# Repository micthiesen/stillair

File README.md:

# stillair

Custom 44-inch direct-drive ceiling fan for quiet overnight air mixing: CubeMars GL100 KV10
gimbal motor, TI MCF8316D sensorless FOC on a custom controller board, ESP32-C6 supervisor
with local-only Apple Home control via Matter (rs-matter), and an independent analog
overspeed backstop.

This repo is the canonical source for everything except the OnShape 3D model:

- [`docs/`](docs/overview.md) — the full design dossier (start at the overview; current work
  state in [docs/STATE.md](docs/STATE.md))
- [`bom/`](bom/README.md) — parts list with purchase tracking
- [`testing/`](testing/README.md) — commissioning matrix with sign-off fields
- [`firmware/`](firmware/) — Rust `no_std` ESP32-C6 supervisor (stub; contract in
  [docs/controls.md](docs/controls.md))
- [`pcb/`](pcb/README.md): authoritative tscircuit source for new boards plus downstream KiCad
  routing and production outputs (requirements in [docs/electrical.md](docs/electrical.md))
- [`cad/`](cad/README.md) — fabrication outputs (specs in [docs/parts.md](docs/parts.md))

Firmware: `cd firmware && cargo build` (stable Rust). Flash the C6 with `cargo run --release` in
`firmware/app` (USB, via `firmware/scripts/flash-app.sh`) or update over the LAN with `esp-ota push`.

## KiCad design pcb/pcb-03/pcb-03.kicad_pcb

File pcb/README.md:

# PCB

PCB design source and production projects. For new boards, committed tscircuit code owns component
definitions, schematic connectivity, board specifications, and placement. KiCad owns downstream
routing, unsupported fabrication detail, checks, and outputs. The complete electrical requirements
are [../docs/electrical.md](../docs/electrical.md), and the V1-to-V2 gate list is at the bottom of
that doc.

## Projects

- `pcb-01/` — the controller board (**PCB-01**). Captured, routed, and ordered from JLCPCB
  2026-07-30 (order W2026073105230212).
- `pcb-01-v2/` — the fresh **PCB-01 V2** controller project. It is intentionally not cloned from
  V1. Capture, placement, routing, silkscreen, and the submission package are complete; its exact
  authority is [`docs/pcb-01-v2.md`](../docs/pcb-01-v2.md) and its order procedure is
  [`pcb-01-v2/fab/ORDERING.md`](pcb-01-v2/fab/ORDERING.md).
- `pcb-02/` — the 24 × 8 mm DRV5033 Hall daughterboard (**PCB-02**). Created 2026-07-30:
  schematic captured (ERC clean), 2-layer board set up (outline, M2 hole pair as the BR-100
  datum, JLCPCB rules). Ships as its own small order — PCB-01 already went out separately.
- `pcb-03/` - the optional 39.75 x 21.00 mm e-paper display bridge (**PCB-03**). It converts PCB-01
  V2's four-wire temperature I2C expansion path to the SPI and sideband signals used by a
  Waveshare 1.54-inch black/white module. Its authority is
  [`docs/pcb-03.md`](../docs/pcb-03.md); it is a two-layer bare board for hand assembly. Upload
  and quote settings are in [`pcb-03/fab/ORDERING.md`](pcb-03/fab/ORDERING.md).

## Tooling and authority

The pinned local tscircuit toolchain lives in this directory. Run its viewer locally so code and
reviewed placement edits remain in the checkout. The **`/pcb` skill** at
[`.agents/skills/pcb/SKILL.md`](../.agents/skills/pcb/SKILL.md) defines authoring, review, initial
handoff, and later ECOs. KiCad 10 and the project-scoped Konnect server remain available only for
the downstream phase.

An initial handoff exports a new KiCad seed into staging. Once routing starts, a new export must
never overwrite the production board. Later tscircuit changes become an explicit stable-identity
ECO, applied through KiCad/Konnect/native APIs and checked to preserve unrelated routes, vias,
zones, rules, and UUID-bound waivers. Each board declares unsupported downstream work in
`design/kicad-augment.json`.

PCB-01, PCB-01 V2, PCB-02, and the already released PCB-03 remain legacy KiCad-authoritative
projects. PCB-03's new `design/` source recreates it only as a workflow validation fixture through
the KiCad handoff boundary.

Fabrication is planned through JLCPCB; JLCPCB assembly vs hand-population is TBD (prefer
footprints/parts in the LCSC catalog where it doesn't compromise the design, so the PCBA
option stays open). The Hall daughterboard (18 × 8 mm, DRV5033) is a second tiny board that
should ride in the same order/panel. A possible V2 reshape to a horizontal donut board is
noted in the handoff doc.

## Human probing map

PCB-01 test-point and connector locations are retained in `pcb-01/probe-map.json`; the human
workflow, ground-domain rules, and temporary-wire policy are in [`docs/probing.md`](../docs/probing.md).
Use `pcb/tools/probe_guide.py TP7`, `pcb/tools/probe_guide.py J8`, or
`pcb/tools/probe_guide.py TP2 --mode resistance` to print a complete one-step instruction. Run
`pcb/tools/probe_guide.py --verify-board` after any layout revision so the retained map cannot silently
drift from the board.

## JLCPCB order config

The bullets below are the historical V1 research record. They do not control PCB-01 V2. V2 uses
the impedance-controlled JLC041621-7628 build, exact POFV attachments, and assembly split in
[`pcb-01-v2/fab/ORDERING.md`](pcb-01-v2/fab/ORDERING.md).

- Standard 4-layer 1.6 mm with the order-form copper dropdown set to **2 oz outer / 1 oz
  inner** (the V1 order did not use a canned JLC04161H stackup; sanity-check the resulting
  dielectric build in the quote tool). ENIG and the Ø3.2 NPTH holes are unrestricted.
- **2 oz raises min trace/space to 0.15–0.16 mm** — check routing under the ESP module
  fits. The common fallback for a ~2 A board is 1 oz outer with ≥1.5–2 mm pours, avoiding
  the 2 oz penalty entirely; decide at capture.
- MCF exposed-pad thermal vias: request **POFV (copper-filled/capped vias)**, drills
  0.25–0.35 mm — a paid special process at 4 layers; budget it.
- Ballpark: ~$80–150 for qty 5 bare boards with the above; 2 oz doesn't block PCBA.

## Footprint/symbol sourcing (researched 2026-07)

Clean pulls from KiCad official libs: ESP32-C6-MINI-1 (needs KiCad ≥8.0.9), GCT USB4105
(note: **top-mount** — confirm against the housing), TC2030-NL, JST PH and SH/SRSS
connectors, Coilcraft LPS4018, Panasonic EEU-FR (parametric CP_Radial), SMC TVS, SOIC-14,
SOT-23 variants.

Needs Ultra Librarian download + datasheet verification: **MCF8316D** (rectangular-body
VQFN-40 RGF — KiCad's stock VQFN-40 is the wrong shape), **TPSM365R6** (RDN QFN-FCMOD).
Hybrid cases: TPS7A1601A (KiCad footprint, UL symbol; check EP copper vs TI's land),
SN74LVC1G74 DCT/SM8 (KiCad's generic SSOP-8 pad span is wider than TI's spec — use TI/UL's).
All TI discrete symbols come from SnapEDA/UL (pinouts are part-specific). Molex: the ordered
headers are the **right-angle** variants (43045-0200, 43650-0300) — use the horizontal
footprints, not vertical.

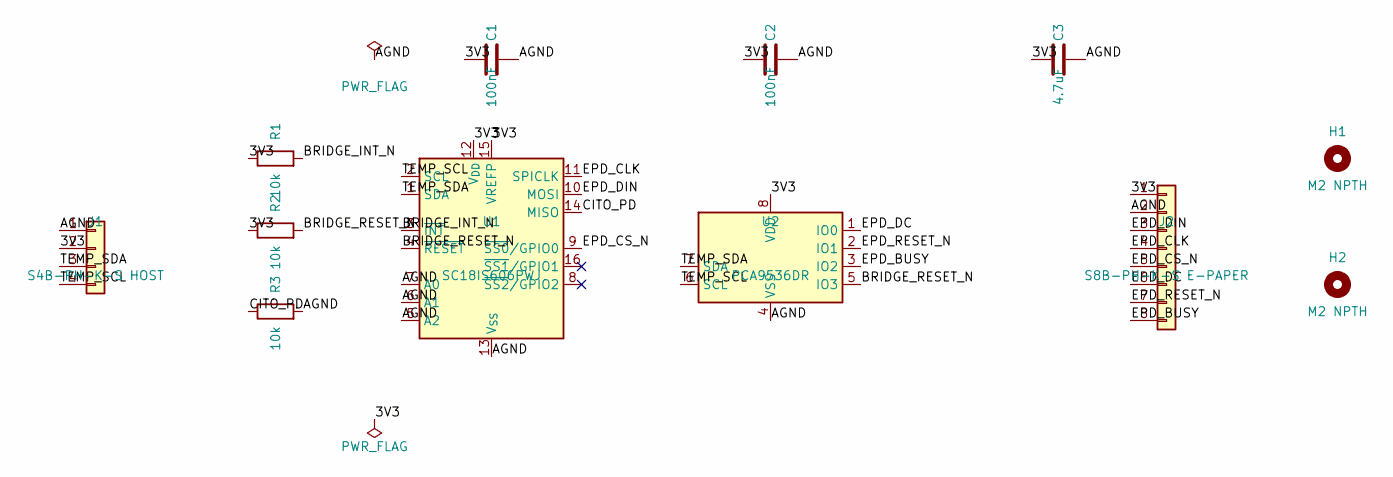
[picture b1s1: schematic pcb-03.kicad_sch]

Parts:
C1, C2: 100nF; C_0603_1608Metric; MPN C0603C104K5RACTU
C3: 4.7uF; C_0603_1608Metric; MPN EMK107ABJ475KA-T
H1, H2: M2 NPTH; MountingHole_2.2mm_M2
J1: S4B-PH-K-S HOST; JST_PH_S4B-PH-K_1x04_P2.00mm_Horizontal; MPN S4B-PH-K-S
J2: S8B-PH-K-S E-PAPER; JST_PH_S8B-PH-K_1x08_P2.00mm_Horizontal; MPN S8B-PH-K-S
R1, R2, R3: 10k; R_0603_1608Metric; MPN PTN0603Y1002BST1
U1: SC18IS606PWJ; TSSOP-16_4.4x5mm_P0.65mm; MPN SC18IS606PWJ
U2: PCA9536DR; SOIC-8_3.9x4.9mm_P1.27mm; MPN PCA9536DR

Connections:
/3V3: C1.1, C2.1, C3.1, J1.2, J2.1, R1.1, R2.1, U1.12 (V_{DD}), U1.15 (VREFP), U2.8 (VDD)
/AGND: C1.2, C2.2, C3.2, J1.1, J2.2, R3.2, U1.5 (A2), U1.6 (A1), U1.7 (A0), U1.13 (V_{SS}), U2.4 (VSS)
/BRIDGE_INT_N: R1.2, U1.3 (~INT)
/BRIDGE_RESET_N: R2.2, U1.4 (~RESET), U2.5 (IO3)
/CITO_PD: R3.1, U1.14 (MISO)
/EPD_BUSY: J2.8, U2.3 (IO2)
/EPD_CLK: J2.4, U1.11 (SPICLK)
/EPD_CS_N: J2.5, U1.9 (~SS0/GPIO0)
/EPD_DC: J2.6, U2.1 (IO0)
/EPD_DIN: J2.3, U1.10 (MOSI)
/EPD_RESET_N: J2.7, U2.2 (IO1)
/TEMP_SCL: J1.4, U1.2 (SCL), U2.6 (SCL)
/TEMP_SDA: J1.3, U1.1 (SDA), U2.7 (SDA)

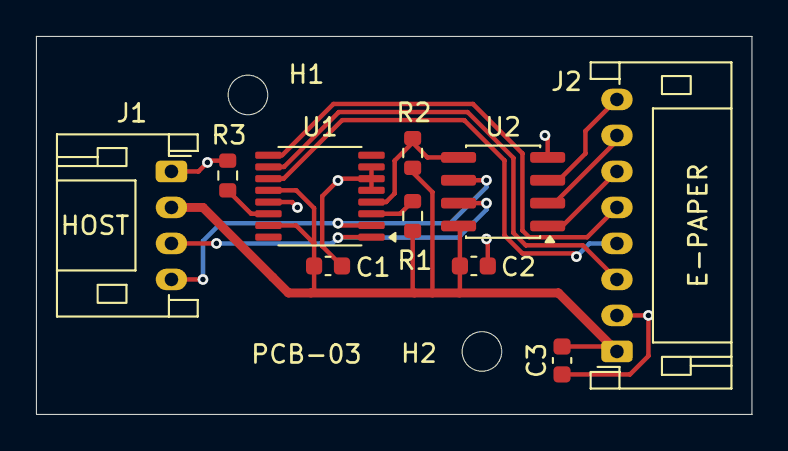
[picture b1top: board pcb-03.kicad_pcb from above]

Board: 2 copper layers, 39.8 x 21.0 mm, 12 parts (0 on the bottom side), 13 nets.

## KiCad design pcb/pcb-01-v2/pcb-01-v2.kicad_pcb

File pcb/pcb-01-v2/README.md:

# PCB-01 V2 KiCad project

Production-intent KiCad 10 project for the 88 x 64 mm PCB-01 V2 controller. The schematic,
footprints, exact ratsnest, four-layer board setup, placement, rule areas, copper zones, keepouts,
fiducials, silkscreen, and assembly metadata are complete. All 166 footprints are on the component
side. Routing and zone fill are complete. The reviewed headless DRC has zero active violations and
zero unconnected items; its 21 exact UUID-bound exceptions are documented in
`../tools/check_drc.py`.

The frozen circuit and layout authority is
[`docs/pcb-01-v2.md`](../../docs/pcb-01-v2.md). Do not import V1 routing, placement, zones, probe
coordinates, or DRC waivers.

## Routing rules retained for review

Open `pcb-01-v2.kicad_pro` and route in the PCB Editor. The concise interactive routing checklist is
<https://mcp.syas.ca/boris/artifacts/art_eon2bpkmslvmtf6wfpa>.

Use the deliberately small routing vocabulary encoded in `pcb-01-v2.kicad_dru`:

| Use | Track | Via |
|---|---:|---:|
| Signals and sensitive analog | 0.20 mm | 0.60/0.30 mm |
| Local rails and 3V3 | 0.50 mm | 0.60/0.30 mm |
| RAW24, VM24, and PGND | 2.00 mm | 1.00/0.50 mm |
| PHASE_U/V/W | 2.00 mm | none |
| USB D+/D- pair | 0.20 mm, 0.20 mm gap | none |

The only narrower power exceptions are the named, tightly bounded U1 and U3 pad-escape areas. The
rules require the complete track item to remain inside the area. Widen immediately after the pad.
U1's three PGND returns use reviewed 0.60/0.30 mm escape vias because its 0.50 mm pin pitch cannot
fit the ordinary 1.00/0.50 mm power via while preserving phase clearance. The headless DRC wrapper
waives only the diameter and drill findings for those three exact via UUIDs.
Do not weaken or delete the PGND routing boundary, antenna keepout, 0.80 mm noisy-to-sensitive
clearance, mounting-hole keepouts, or fiducial keepouts to complete routing.

The stack is 1.6 mm FR-4, four layers, with 2 oz outer and 1 oz inner copper. In1.Cu is the AGND
plane. In2.Cu contains the 3V3 region and motor-region copper defined in the board. Ordinary minimum
clearance is 0.20 mm; 24 V and motor-phase clearance is 0.25 mm; copper-to-edge is 0.50 mm.

## Current verification state

- ERC: zero violations.
- Schematic parity: 159 refs, 78 named nets, and 411 endpoints match the frozen schedule.
- Board: 166 top-side footprints, completed routing, filled zones, and no unconnected items.
- DRC: zero active violations and zero unconnected items, with 21 exact reviewed exceptions for
  bounded pad escapes and three U1 PGND escape vias.
- Probe map: 31 test points and four pin-mapped connectors match the board.
- Assembly export: 55 machine BOM lines, 119 top-side CPL placements, and six hand refs.

After any board edit, refill all zones and rerun the complete release generator. It refuses to emit
orderable Gerbers if ERC, schematic parity, DRC, or probe-map parity fails.

Useful checks from the repository root:

```bash
kicad-cli sch erc pcb/pcb-01-v2/pcb-01-v2.kicad_sch
python3 pcb/tools/check_drc.py
kicad-cli sch export netlist --output /tmp/pcb-01-v2.net pcb/pcb-01-v2/pcb-01-v2.kicad_sch
python3 pcb/tools/check_v2_capture.py /tmp/pcb-01-v2.net
python3 pcb/tools/probe_guide.py --map pcb/pcb-01-v2/probe-map.json \
  --board pcb/pcb-01-v2/pcb-01-v2.kicad_pcb --verify-board
python3 pcb/tools/jlc_fab.py pcb-01-v2
```

## Fabrication handoff

The tracked `fab/` directory contains the exact LCSC map, assembly/hand manifests, machine BOM,
CPL, POFV coordinates, fabrication notes, and a generated four-page assembly locator. U1's twelve
0.30 mm pad-41 holes require epoxy fill and copper capping. U1 pad 41 retains its submitted top
solder-mask aperture for soldering, with no separate bottom aperture. The Excellon and KiCad
coordinate conventions are identified in the generated POFV attachments. U3 pads 4 and 5 are
mask-defined and require JLC engineering confirmation.

Run `python3 pcb/tools/jlc_fab.py pcb-01-v2` immediately before upload, verify
`fab/release-manifest.sha256`, inspect the generated Gerbers, drill map, BOM, CPL, POFV attachments,
and assembly orientation guide, then follow `fab/ORDERING.md` and `fab/fabrication-notes.md`.

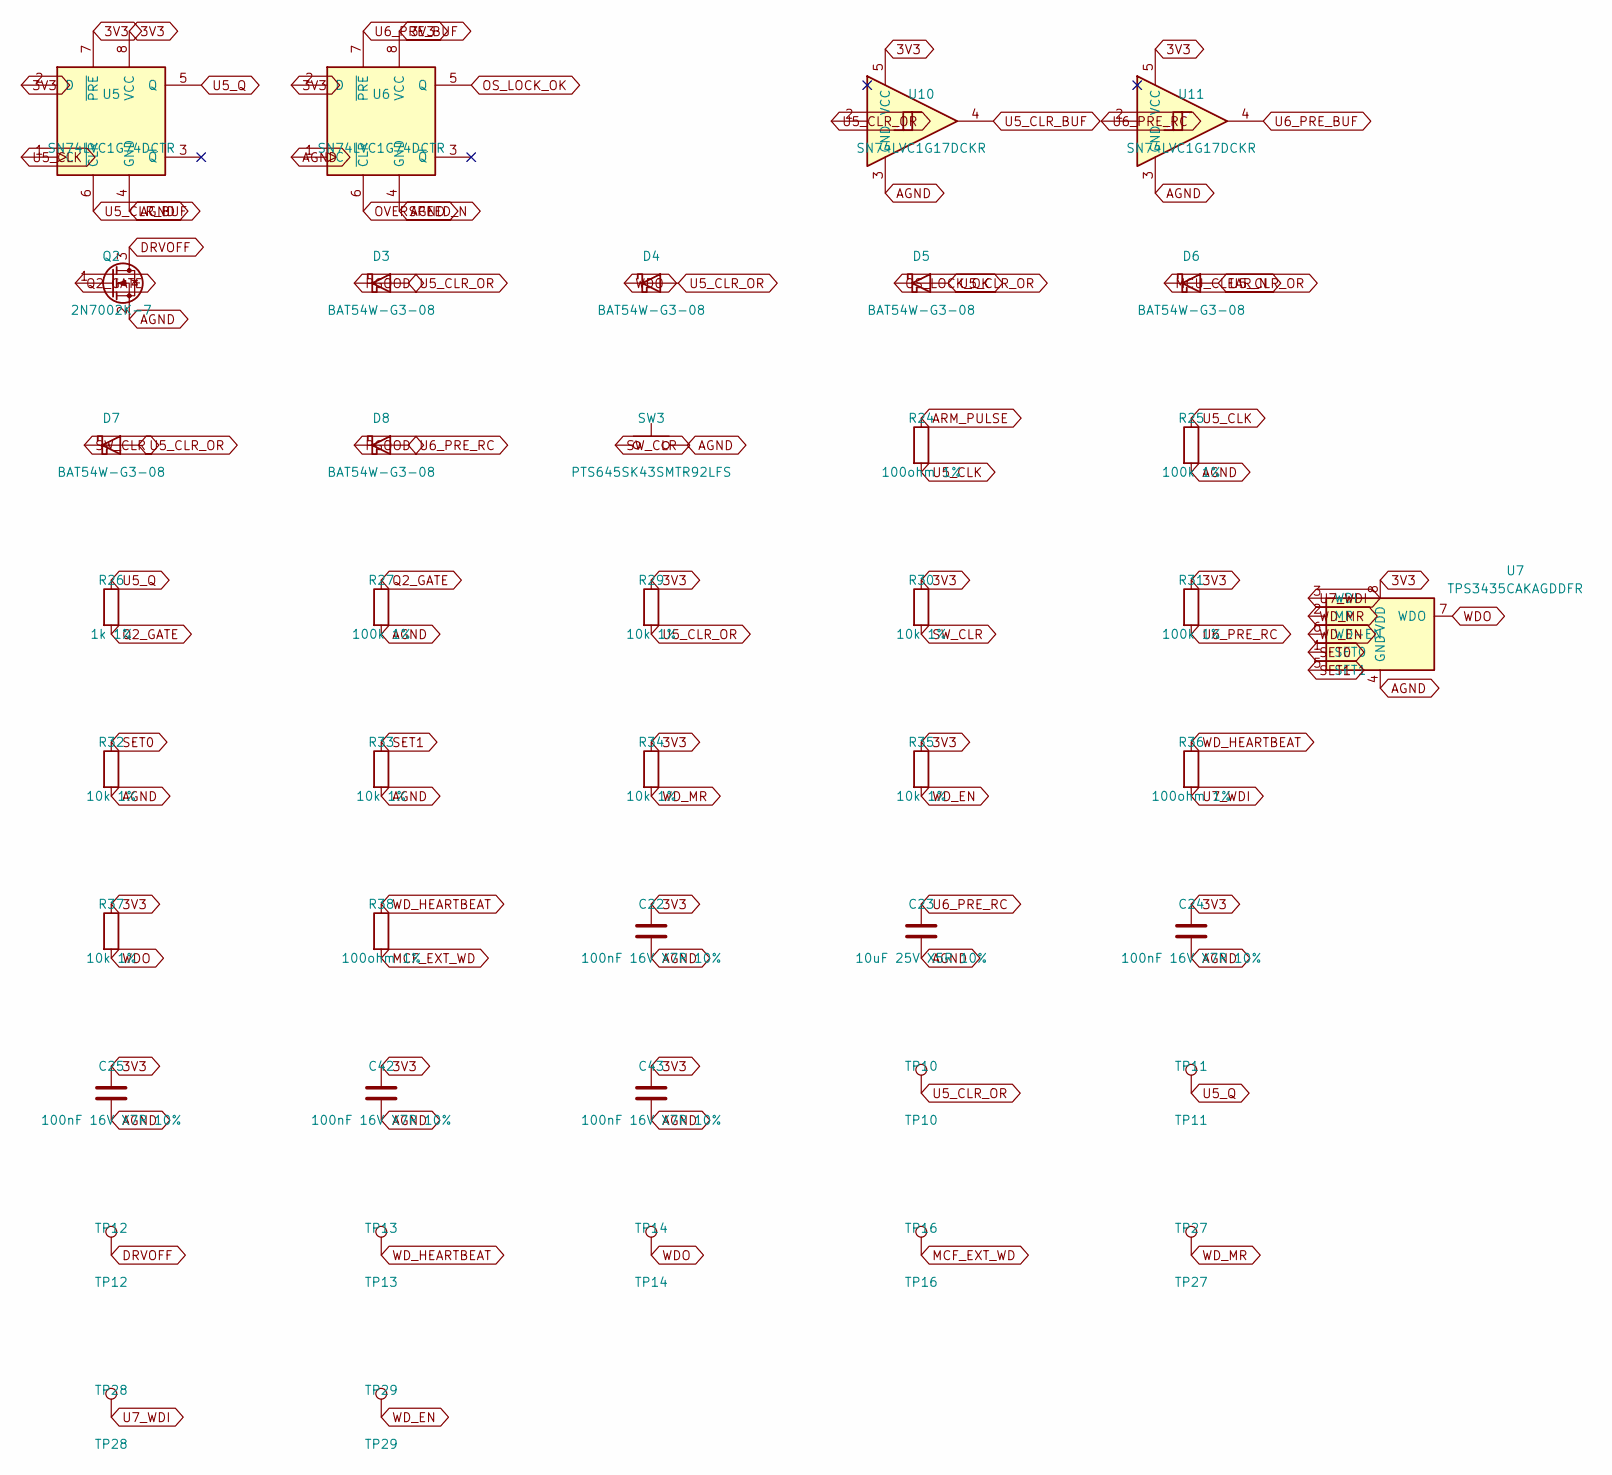
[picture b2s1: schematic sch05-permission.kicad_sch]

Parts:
C22, C24, C25, C42, C43: 100nF 16V X7R 10%; C_0402_1005Metric
C23: 10uF 25V X5R 10%; C_0805_2012Metric
D3, D4, D5, D6, D7, D8: BAT54W-G3-08; D_SOD-123
Q2: 2N7002K-7; SOT-23
R24, R36, R38: 100ohm 1%; R_0402_1005Metric
R25, R27, R31: 100k 1%; R_0402_1005Metric
R26: 1k 1%; R_0402_1005Metric
R29, R30, R32, R33, R34, R35, R37: 10k 1%; R_0402_1005Metric
SW3: PTS645SK43SMTR92LFS; SW_SPST_PTS645Sx43SMTR92
TP10: TP10; TestHole_2.4mm_PTH1.0mm
TP11: TP11; TestHole_2.4mm_PTH1.0mm
TP12: TP12; TestHole_2.4mm_PTH1.0mm
TP13: TP13; TestHole_2.4mm_PTH1.0mm
TP14: TP14; TestHole_2.4mm_PTH1.0mm
TP16: TP16; TestHole_2.4mm_PTH1.0mm
TP27: TP27; TestHole_2.4mm_PTH1.0mm
TP28: TP28; TestHole_2.4mm_PTH1.0mm
TP29: TP29; TestHole_2.4mm_PTH1.0mm
U5, U6: SN74LVC1G74DCTR; TI_SM8_DCT0008A
U7: TPS3435CAKAGDDFR; SOT-23-8_P0.65mm_Clearance0.20
U10, U11: SN74LVC1G17DCKR; SOT-353_SC-70-5

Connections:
3V3: C22.1, C24.1, C25.1, C42.1, C43.1, R29.1, R30.1, R31.1, R34.1, R35.1, R37.1, U5.2 (D), U5.7 (~PRE), U5.8 (VCC), U6.2 (D), U6.8 (VCC), U7.8 (VDD), U10.5 (VCC), U11.5 (VCC); also elsewhere on the board
ARM_PULSE: R24.1; also elsewhere on the board
DRVOFF: Q2.3 (D), TP12.1 (1_1); also elsewhere on the board
MCF_EXT_WD: R38.2, TP16.1 (1_1); also elsewhere on the board
MCU_CLEAR_N: D6.1 (K); also elsewhere on the board
OS_LOCK_OK: D5.1 (K), U6.5 (Q)
OVERSPEED_N: U6.6 (~CLR); also elsewhere on the board
PGOOD: D3.1 (K), D8.1 (K); also elsewhere on the board
Q2_GATE: Q2.1 (G), R26.2, R27.1
SET0: R32.1, U7.1 (SET0)
SET1: R33.1, U7.5 (SET1)
SW_CLR: D7.1 (K), R30.2, SW3.1
U5_CLK: R24.2, R25.1, U5.1 (C)
U5_CLR_BUF: U5.6 (~CLR), U10.4
U5_CLR_OR: D3.2 (A), D4.2 (A), D5.2 (A), D6.2 (A), D7.2 (A), R29.2, TP10.1 (1_1), U10.2
U5_Q: R26.1, TP11.1 (1_1), U5.5 (Q)
U6_PRE_BUF: U6.7 (~PRE), U11.4
U6_PRE_RC: C23.1, D8.2 (A), R31.2, U11.2
U7_WDI: R36.2, TP28.1 (1_1), U7.3 (WDI)
WDO: D4.1 (K), R37.2, TP14.1 (1_1), U7.7 (WDO); also elsewhere on the board
WD_EN: R35.2, TP29.1 (1_1), U7.6 (WD-EN)
WD_HEARTBEAT: R36.1, R38.1, TP13.1 (1_1); also elsewhere on the board
WD_MR: R34.2, TP27.1 (1_1), U7.2 (MR)

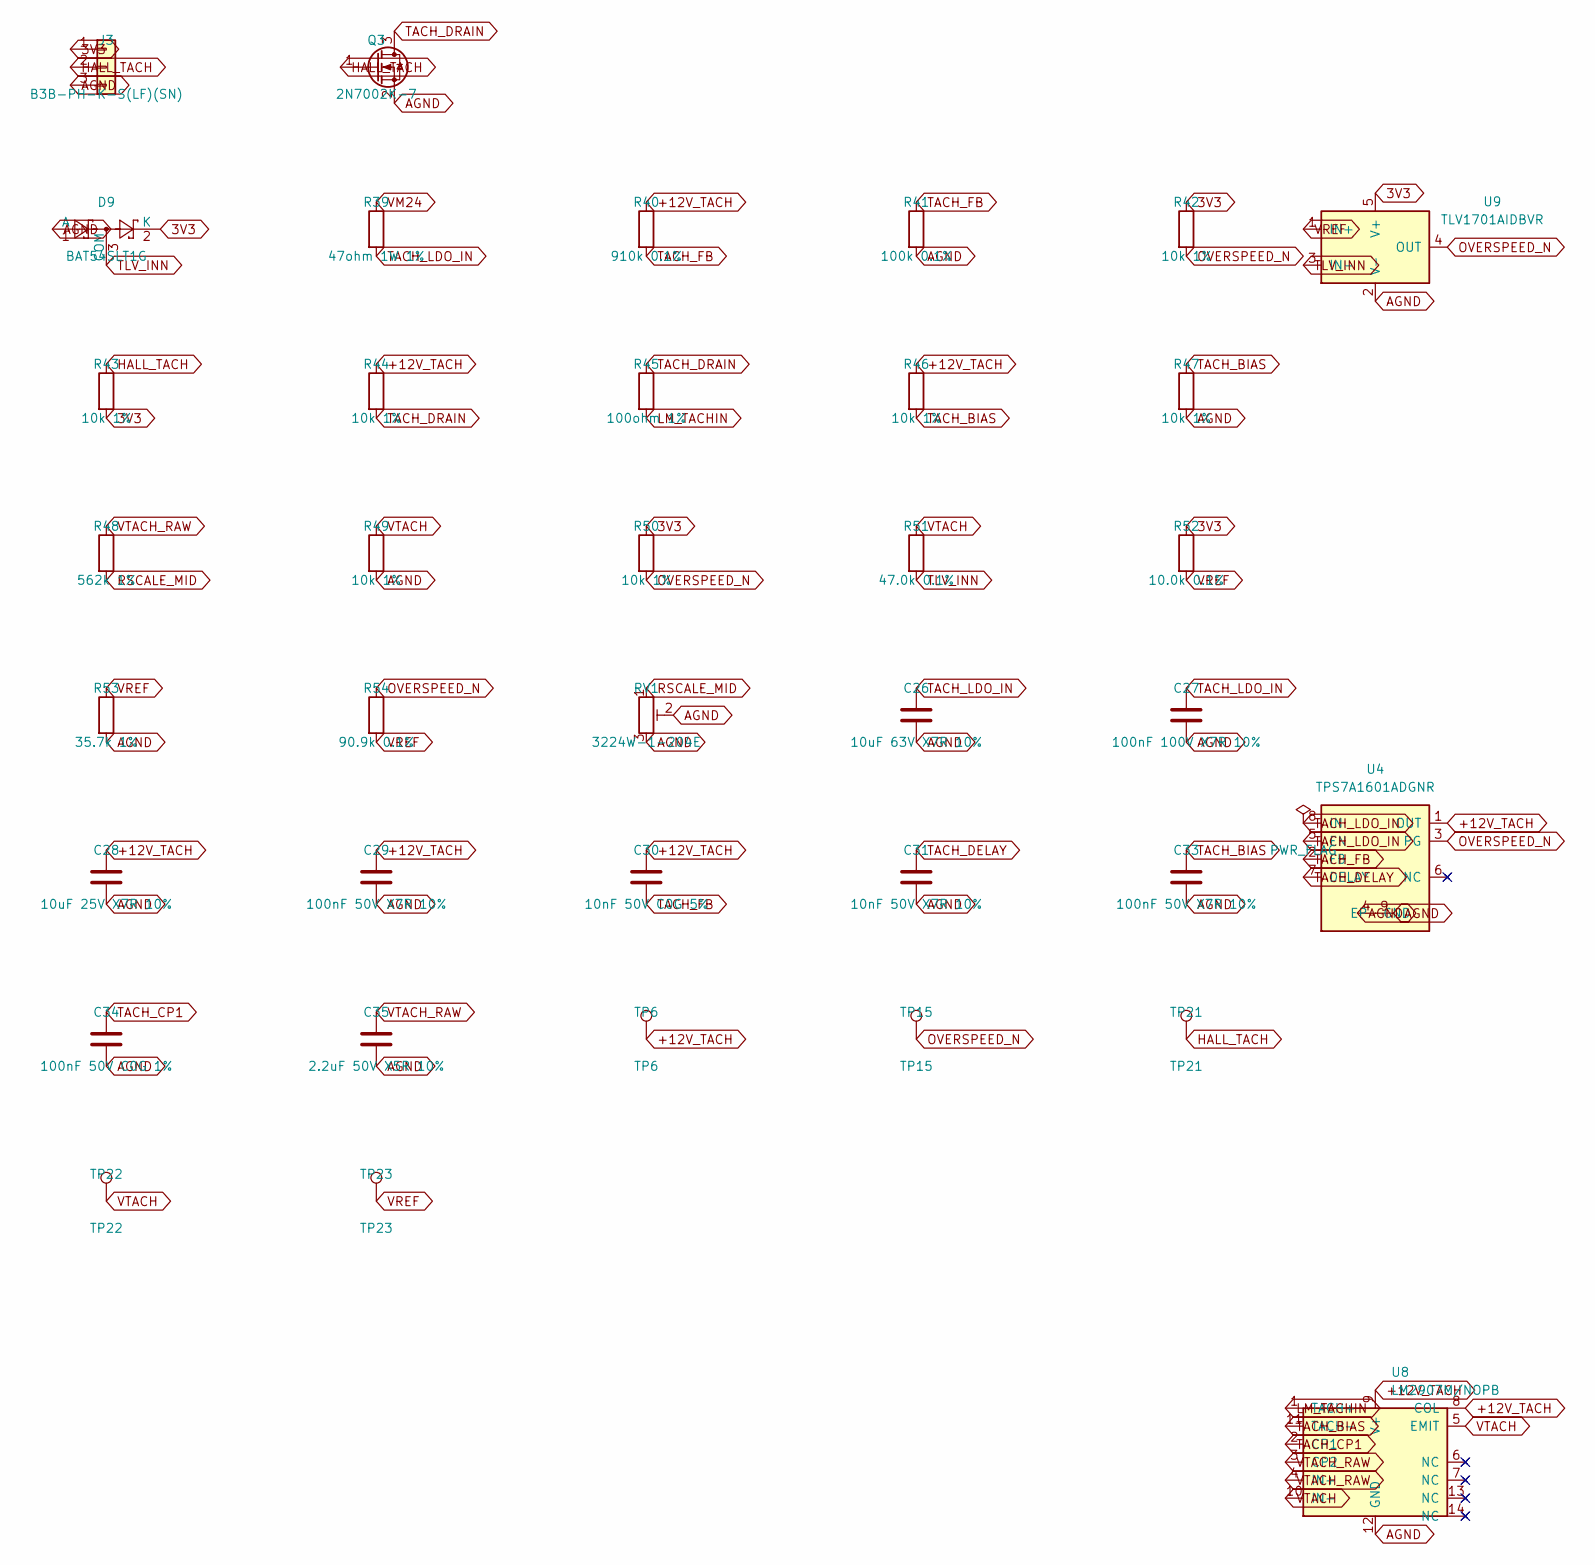
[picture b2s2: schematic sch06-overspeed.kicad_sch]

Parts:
C26: 10uF 63V X7R 10%; C_1210_3225Metric
C27: 100nF 100V X7R 10%; C_0805_2012Metric
C28: 10uF 25V X7R 10%; C_1210_3225Metric
C29, C33: 100nF 50V X7R 10%; C_0603_1608Metric
C30: 10nF 50V C0G 5%; C_0603_1608Metric
C31: 10nF 50V X7R 10%; C_0402_1005Metric
C34: 100nF 50V C0G 1%; C_1206_3216Metric
C35: 2.2uF 50V X5R 10%; C_0805_2012Metric
D9: BAT54SLT1G; SOT-23
J3: B3B-PH-K-S(LF)(SN); JST_PH_B3B-PH-K_1x03_P2.00mm_Vertical
Q3: 2N7002K-7; SOT-23
R39: 47ohm 1W 1%; R_2512_6332Metric
R40: 910k 0.1%; R_0402_1005Metric
R41: 100k 0.1%; R_0402_1005Metric
R42, R43, R44, R46, R47, R49, R50: 10k 1%; R_0402_1005Metric
R45: 100ohm 1%; R_0402_1005Metric
R48: 562k 1%; R_0402_1005Metric
R51: 47.0k 0.1%; R_0402_1005Metric
R52: 10.0k 0.1%; R_0402_1005Metric
R53: 35.7k 1%; R_0402_1005Metric
R54: 90.9k 0.1%; R_0402_1005Metric
RV1: 3224W-1-204E; Potentiometer_Bourns_3224W_Vertical
TP6: TP6; TestHole_2.4mm_PTH1.0mm
TP15: TP15; TestHole_2.4mm_PTH1.0mm
TP21: TP21; TestHole_2.4mm_PTH1.0mm
TP22: TP22; TestHole_2.4mm_PTH1.0mm
TP23: TP23; TestHole_2.4mm_PTH1.0mm
U4: TPS7A1601ADGNR; MSOP-8-1EP_3x3mm_P0.65mm_EP1.68x1.88mm
U8: LM2907M/NOPB; SOIC-14_3.9x8.7mm_P1.27mm
U9: TLV1701AIDBVR; SOT-23-5

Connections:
3V3: D9.2 (K), J3.1, R42.1, R43.2, R50.1, R52.1, U9.5 (V+); also elsewhere on the board
+12V_TACH: C28.1, C29.1, C30.1, R40.1, R44.1, R46.1, TP6.1 (1_1), U4.1 (OUT), U8.8 (COL), U8.9 (V+)
HALL_TACH: J3.2, Q3.1 (G), R43.1, TP21.1 (1_1); also elsewhere on the board
LM_TACHIN: R45.2, U8.1 (TACH+)
OVERSPEED_N: R42.2, R50.2, R54.1, TP15.1 (1_1), U4.3 (PG), U9.4 (OUT); also elsewhere on the board
RSCALE_MID: R48.2, RV1.1
TACH_BIAS: C33.1, R46.2, R47.1, U8.11 (TACH-)
TACH_CP1: C34.1, U8.2 (CP1)
TACH_DELAY: C31.1, U4.7 (DELAY)
TACH_DRAIN: Q3.3 (D), R44.2, R45.1
TACH_FB: C30.2, R40.2, R41.1, U4.2 (FB)
TACH_LDO_IN: C26.1, C27.1, R39.2, U4.5 (EN), U4.8 (IN)
TLV_INN: D9.3 (COM), R51.2, U9.3 (IN-)
VREF: R52.2, R53.1, R54.2, TP23.1 (1_1), U9.1 (IN+)
VTACH: R49.1, R51.1, TP22.1 (1_1), U8.5 (EMIT), U8.10 (IN-)
VTACH_RAW: C35.1, R48.1, U8.3 (CP2), U8.4 (IN+)

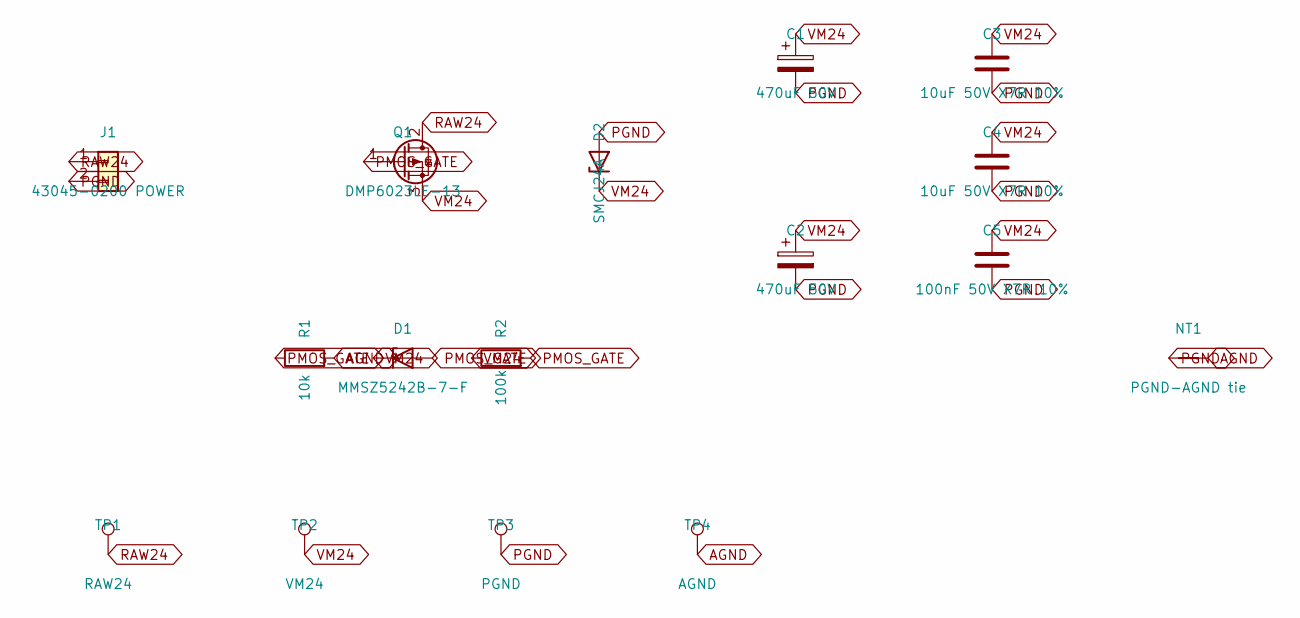
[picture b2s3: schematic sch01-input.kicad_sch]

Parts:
C1, C2: 470uF 50V; CP_Radial_D10.0mm_P5.00mm; MPN EEU-FR1H471
C3, C4: 10uF 50V X7R 10%; C_1210_3225Metric; LCSC C2918502
C5: 100nF 50V X7R 10%; C_0603_1608Metric; LCSC C14663
D1: MMSZ5242B-7-F; D_SOD-123; MPN MMSZ5242B-7-F; LCSC C500776
D2: SMCJ24A; D_SMC; MPN SMCJ24A; LCSC C135154
J1: 43045-0200 POWER; Molex_Micro-Fit_3.0_43045-0200_2x01_P3.00mm_Horizontal; MPN 43045-0200
NT1: PGND-AGND tie; NetTie-2_SMD_Pad2.0mm
Q1: DMP6023LE-13; SOT-223-3_TabPin2; MPN DMP6023LE-13; LCSC C154901
R1: 10k; R_0402_1005Metric; MPN 0402WGF1002TCE; LCSC C25744
R2: 100k; R_0402_1005Metric; LCSC C25741
TP1: RAW24; TestHole_2.4mm_PTH1.0mm
TP2: VM24; TestHole_2.4mm_PTH1.0mm
TP3: PGND; TestHole_2.4mm_PTH1.0mm
TP4: AGND; TestHole_2.4mm_PTH1.0mm

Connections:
PMOS_GATE: D1.2 (A), Q1.1 (G), R1.1, R2.2
RAW24: J1.1, Q1.2 (D), TP1.1 (1_1)

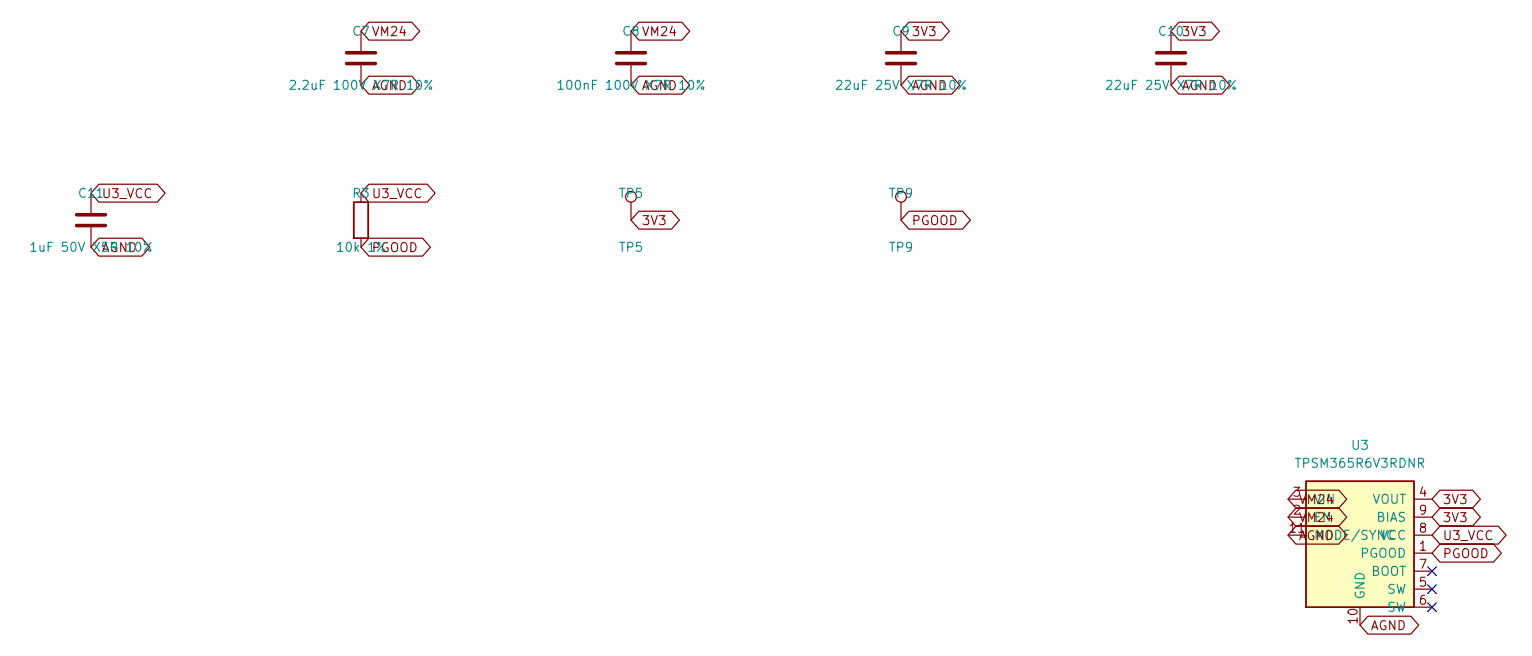
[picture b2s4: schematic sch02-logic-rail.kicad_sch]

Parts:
C7: 2.2uF 100V X7R 10%; C_1210_3225Metric
C8: 100nF 100V X7R 10%; C_0805_2012Metric
C9, C10: 22uF 25V X7R 10%; C_1210_3225Metric
C11: 1uF 50V X5R 10%; C_0603_1608Metric
R3: 10k 1%; R_0402_1005Metric
TP5: TP5; TestHole_2.4mm_PTH1.0mm
TP9: TP9; TestHole_2.4mm_PTH1.0mm
U3: TPSM365R6V3RDNR; TPSM365R6_RDN0011A

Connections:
3V3: C9.1, C10.1, TP5.1 (1_1), U3.4 (VOUT), U3.9 (BIAS); also elsewhere on the board
PGOOD: R3.2, TP9.1 (1_1), U3.1 (PGOOD); also elsewhere on the board
U3_VCC: C11.1, R3.1, U3.8 (VCC)

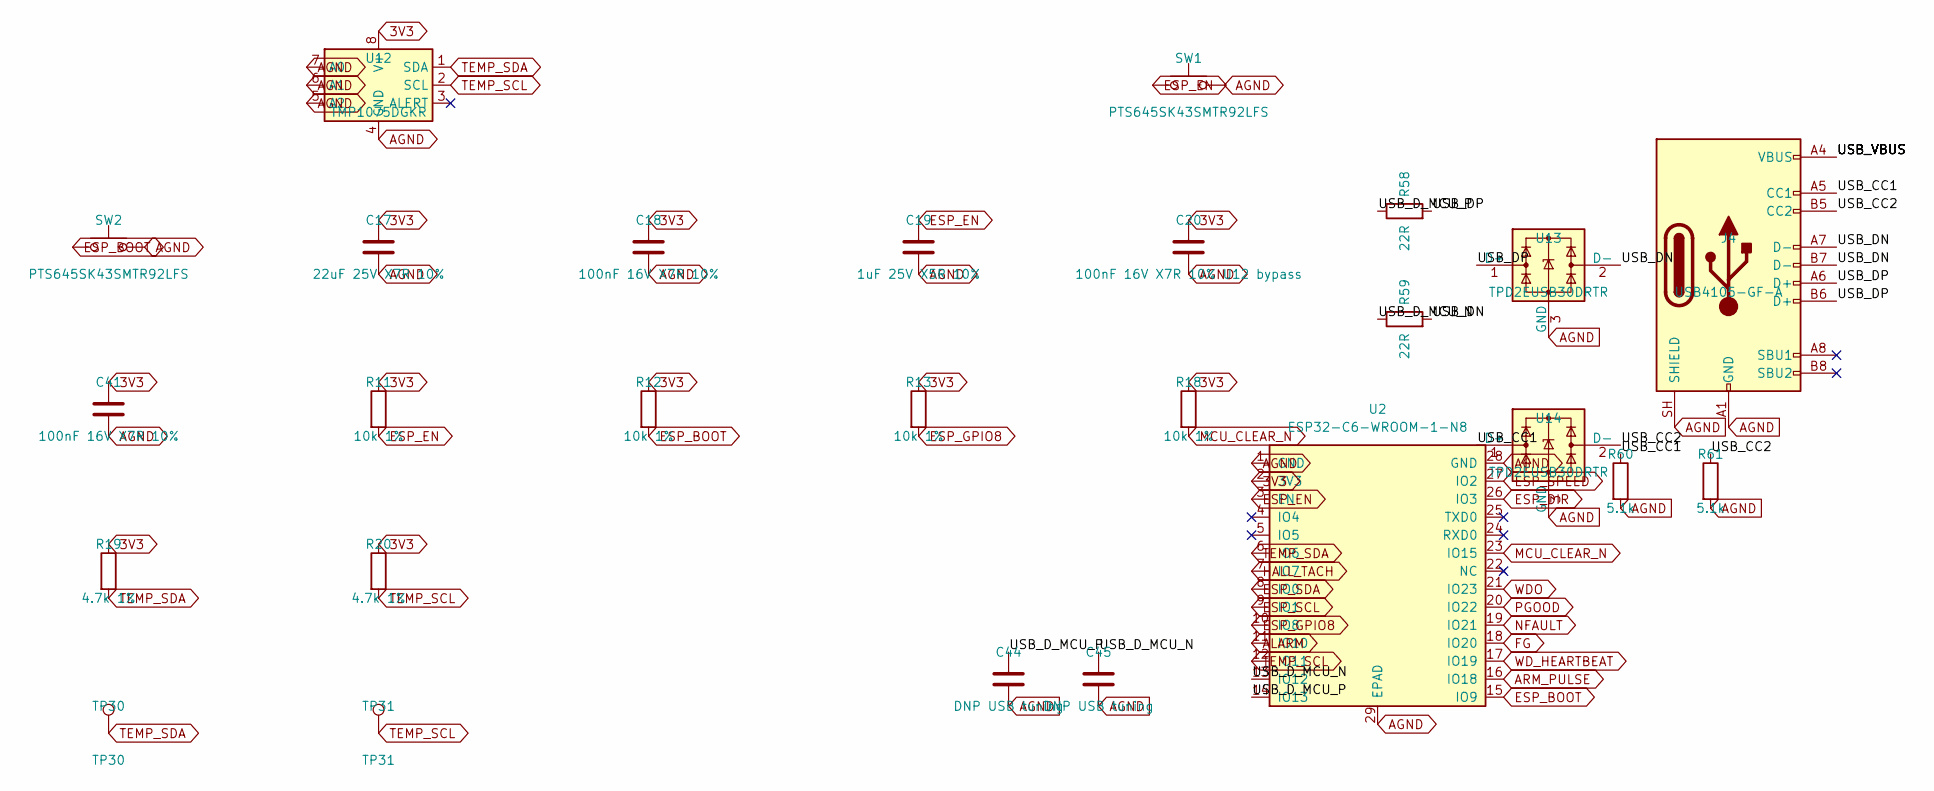
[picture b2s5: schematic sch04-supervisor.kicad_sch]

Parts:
C17: 22uF 25V X7R 10%; C_1210_3225Metric
C18, C41: 100nF 16V X7R 10%; C_0402_1005Metric
C19: 1uF 25V X5R 10%; C_0402_1005Metric
C20: 100nF 16V X7R 10% U12 bypass; C_0402_1005Metric
C44, C45: DNP USB tuning; C_0402_1005Metric
J4: USB4105-GF-A; USB_C_Receptacle_GCT_USB4105-xx-A_16P_TopMnt_Horizontal; MPN USB4105-GF-A; LCSC C3020560
R11, R12, R13, R18: 10k 1%; R_0402_1005Metric
R19, R20: 4.7k 1%; R_0402_1005Metric
R58, R59: 22R; R_0402_1005Metric; MPN 0402WGF220JTCE; LCSC C25092
R60, R61: 5.1k; R_0402_1005Metric; MPN 0402WGF5101TCE; LCSC C25905
SW1, SW2: PTS645SK43SMTR92LFS; SW_SPST_PTS645Sx43SMTR92
TP30: TP30; TestHole_2.4mm_PTH1.0mm
TP31: TP31; TestHole_2.4mm_PTH1.0mm
U2: ESP32-C6-WROOM-1-N8; ESP32-C6-WROOM-1
U12: TMP1075DGKR; VSSOP-8_3x3mm_P0.65mm_Clearance0.20
U13, U14: TPD2EUSB30DRTR; Texas_DRT-3; MPN TPD2EUSB30DRTR; LCSC C97502

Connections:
3V3: C17.1, C18.1, C20.1, C41.1, R11.1, R12.1, R13.1, R18.1, R19.1, R20.1, U2.2 (3V3), U12.8 (V+); also elsewhere on the board
/SCH-04 Supervisor + Service/USB_CC1: J4.A5 (CC1), R60.1, U14.1 (D+)
/SCH-04 Supervisor + Service/USB_CC2: J4.B5 (CC2), R61.1, U14.2 (D-)
/SCH-04 Supervisor + Service/USB_DN: J4.A7 (D-), J4.B7 (D-), R59.2, U13.2 (D-)
/SCH-04 Supervisor + Service/USB_DP: J4.A6 (D+), J4.B6 (D+), R58.2, U13.1 (D+)
/SCH-04 Supervisor + Service/USB_D_MCU_N: C45.1, R59.1, U2.13 (IO12)
/SCH-04 Supervisor + Service/USB_D_MCU_P: C44.1, R58.1, U2.14 (IO13)
/SCH-04 Supervisor + Service/USB_VBUS: J4.A4 (VBUS), J4.A9 (VBUS), J4.B4 (VBUS), J4.B9 (VBUS)
ALARM: U2.11 (IO10); also elsewhere on the board
ARM_PULSE: U2.16 (IO18); also elsewhere on the board
ESP_BOOT: R12.2, SW2.1, U2.15 (IO9)
ESP_DIR: U2.26 (IO3); also elsewhere on the board
ESP_EN: C19.1, R11.2, SW1.1, U2.3 (EN)
ESP_GPIO8: R13.2, U2.10 (IO8)
ESP_SCL: U2.9 (IO1); also elsewhere on the board
ESP_SDA: U2.8 (IO0); also elsewhere on the board
ESP_SPEED: U2.27 (IO2); also elsewhere on the board
FG: U2.18 (IO20); also elsewhere on the board
HALL_TACH: U2.7 (IO7); also elsewhere on the board
MCU_CLEAR_N: R18.2, U2.23 (IO15); also elsewhere on the board
NFAULT: U2.19 (IO21); also elsewhere on the board
PGOOD: U2.20 (IO22); also elsewhere on the board
TEMP_SCL: R20.2, TP31.1 (1_1), U2.12 (IO11), U12.2 (SCL)
TEMP_SDA: R19.2, TP30.1 (1_1), U2.6 (IO6), U12.1 (SDA)
WDO: U2.21 (IO23); also elsewhere on the board
WD_HEARTBEAT: U2.17 (IO19); also elsewhere on the board

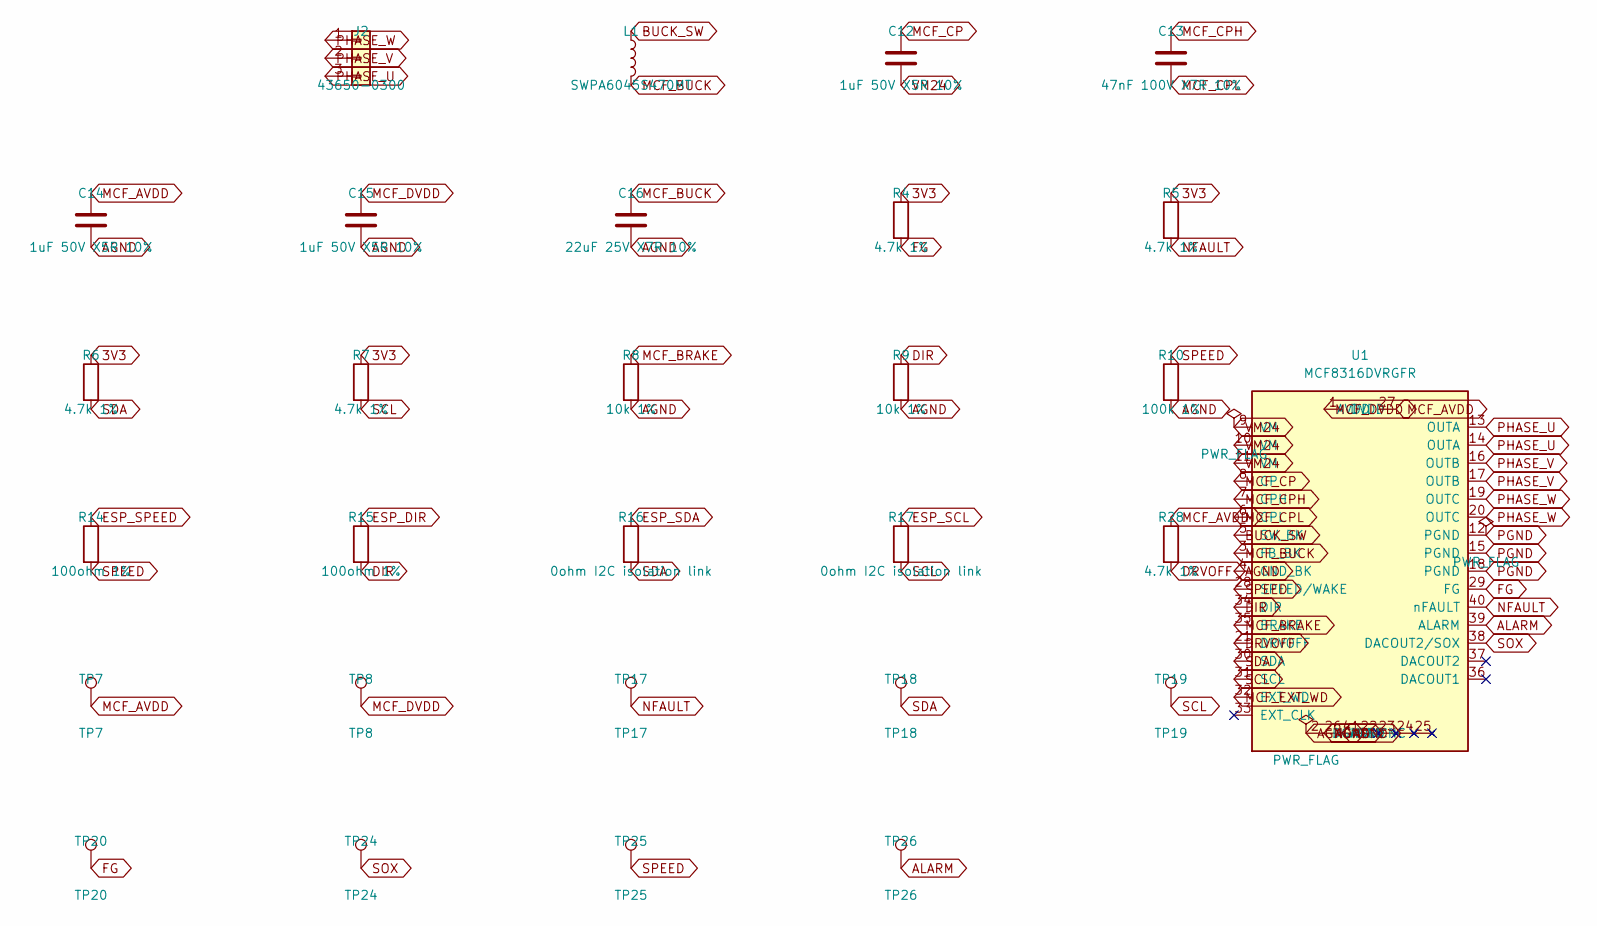
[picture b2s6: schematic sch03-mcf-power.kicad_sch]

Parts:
C12, C14, C15: 1uF 50V X5R 10%; C_0603_1608Metric
C13: 47nF 100V X7R 10%; C_0805_2012Metric
C16: 22uF 25V X7R 10%; C_1210_3225Metric
J2: 43650-0300; Molex_Micro-Fit_3.0_43650-0300_1x03_P3.00mm_Horizontal
L1: SWPA6045S470MT; L_Sunlord_SWPA6045S
R4, R5, R6, R7, R28: 4.7k 1%; R_0402_1005Metric
R8, R9: 10k 1%; R_0402_1005Metric
R10: 100k 1%; R_0402_1005Metric
R14, R15: 100ohm 1%; R_0402_1005Metric
R16, R17: 0ohm I2C isolation link; R_0402_1005Metric
TP7: TP7; TestHole_2.4mm_PTH1.0mm
TP8: TP8; TestHole_2.4mm_PTH1.0mm
TP17: TP17; TestHole_2.4mm_PTH1.0mm
TP18: TP18; TestHole_2.4mm_PTH1.0mm
TP19: TP19; TestHole_2.4mm_PTH1.0mm
TP20: TP20; TestHole_2.4mm_PTH1.0mm
TP24: TP24; TestHole_2.4mm_PTH1.0mm
TP25: TP25; TestHole_2.4mm_PTH1.0mm
TP26: TP26; TestHole_2.4mm_PTH1.0mm
U1: MCF8316DVRGFR; MCF8316D_RGF0040E

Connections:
3V3: R4.1, R5.1, R6.1, R7.1; also elsewhere on the board
ALARM: TP26.1 (1_1), U1.39 (ALARM); also elsewhere on the board
BUCK_SW: L1.1, U1.5 (SW_BK)
DIR: R9.1, R15.2, U1.34 (DIR)
DRVOFF: R28.2, U1.21 (DRVOFF); also elsewhere on the board
ESP_DIR: R15.1; also elsewhere on the board
ESP_SCL: R17.1; also elsewhere on the board
ESP_SDA: R16.1; also elsewhere on the board
ESP_SPEED: R14.1; also elsewhere on the board
FG: R4.2, TP20.1 (1_1), U1.29 (FG); also elsewhere on the board
MCF_AVDD: C14.1, R28.1, TP7.1 (1_1), U1.27 (AVDD)
MCF_BRAKE: R8.1, U1.35 (BRAKE)
MCF_BUCK: C16.1, L1.2, U1.3 (FB_BK)
MCF_CP: C12.1, U1.8 (CP)
MCF_CPH: C13.1, U1.7 (CPH)
MCF_CPL: C13.2, U1.6 (CPL)
MCF_DVDD: C15.1, TP8.1 (1_1), U1.1 (DVDD)
MCF_EXT_WD: U1.32 (EXT_WD); also elsewhere on the board
NFAULT: R5.2, TP17.1 (1_1), U1.40 (nFAULT); also elsewhere on the board
PHASE_U: J2.3, U1.13 (OUTA), U1.14 (OUTA)
PHASE_V: J2.2, U1.16 (OUTB), U1.17 (OUTB)
PHASE_W: J2.1, U1.19 (OUTC), U1.20 (OUTC)
SCL: R7.2, R17.2, TP19.1 (1_1), U1.31 (SCL)
SDA: R6.2, R16.2, TP18.1 (1_1), U1.30 (SDA)
SOX: TP24.1 (1_1), U1.38 (DACOUT2/SOX)
SPEED: R10.1, R14.2, TP25.1 (1_1), U1.28 (SPEED/WAKE)

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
